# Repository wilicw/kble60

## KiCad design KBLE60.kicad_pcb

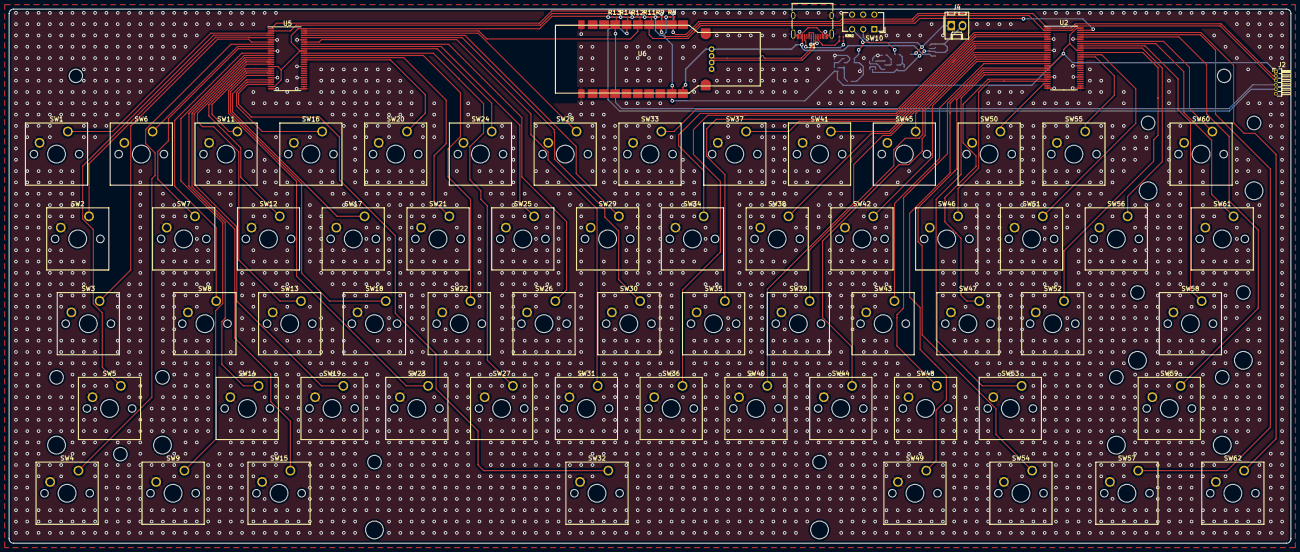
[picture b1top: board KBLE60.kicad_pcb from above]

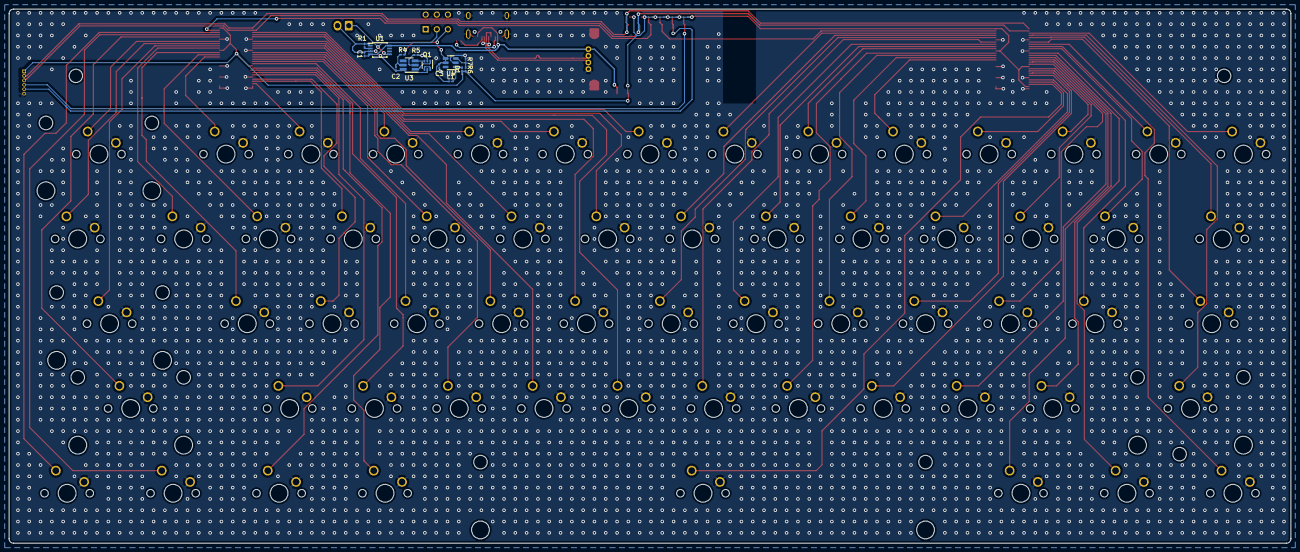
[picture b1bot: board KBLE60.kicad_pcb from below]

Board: 2 copper layers, 288.0 x 120.0 mm, 90 parts (14 on the bottom side), 85 nets.

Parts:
C1: 10u; C_0201_0603Metric_Pad0.64x0.40mm_HandSolder
C2, C3: 22u; C_0201_0603Metric_Pad0.64x0.40mm_HandSolder
D1: D_Schottky_Small; D_0201_0603Metric_Pad0.64x0.40mm_HandSolder
J1: USB_C_Receptacle_USB2.0; USB_C_Receptacle_XKB_U262-16XN-4BVC11
J2: Ext_pin; PinHeader_1x06_P1.00mm_Horizontal
J4: Battery; Molex_KK-254_AE-6410-02A_1x02_P2.54mm_Vertical
L1: 22u; L_0201_0603Metric_Pad0.64x0.40mm_HandSolder
Q1: Q_Dual_NMOS_G1S2G2D2S1D1; SOT-363_SC-70-6
R1, R7, R11, R12, R13, R14: 2k; R_0201_0603Metric_Pad0.64x0.40mm_HandSolder
R2, R3: 5k1; R_0201_0603Metric_Pad0.64x0.40mm_HandSolder
R4: 100; R_0201_0603Metric_Pad0.64x0.40mm_HandSolder
R5: 1k; R_0201_0603Metric_Pad0.64x0.40mm_HandSolder
R6: 10k; R_0201_0603Metric_Pad0.64x0.40mm_HandSolder
R8, R9: 4k7; R_0201_0603Metric_Pad0.64x0.40mm_HandSolder
SW1, SW6, SW7, SW8, SW11, SW12, SW13, SW14, SW16, SW17, SW18, SW19, SW20, SW21, SW22, SW23, SW24, SW25, SW26, SW27, SW28, SW29, SW30, SW31, SW33, SW34, SW35, SW36, SW37, SW38, SW39, SW40, SW41, SW42, SW43, SW44, SW45, SW46, SW47, SW48, SW50, SW51, SW52, SW53, SW55, SW56: SW_Push; SW_Cherry_MX_1.00u_PCB
SW2, SW61: SW_Push; SW_Cherry_MX_1.50u_PCB
SW3: SW_Push; SW_Cherry_MX_1.75u_PCB
SW4, SW9, SW15, SW49, SW54, SW57, SW62: SW_Push; SW_Cherry_MX_1.25u_PCB
SW5, SW58: SW_Push; SW_Cherry_MX_2.25u_PCB
SW10: SW_DPDT_x2; SW_CuK_JS202011AQN_DPDT_Angled
SW32: SW_Push; SW_Cherry_MX_6.25u_PCB
SW59: SW_Push; SW_Cherry_MX_2.75u_PCB
SW60: SW_Push; SW_Cherry_MX_2.00u_PCB
U1: tp4056; TSSOP-8_3x3mm_P0.65mm
U2, U5: PCA9506DGG,512; TSSOP-56_6.1x14mm_P0.5mm
U3: fs312f; SOT-23-6_Handsoldering
U4: MT3608; SOT-23-6
U6: nRF52840_dongle

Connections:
+BATT: J4.1, SW10.2 (B), U1.5 (BAT)
+VSW: C3.1, L1.1, R4.1, SW10.3 (C), U4.4 (EN), U4.5 (IN)
-BATT: C1.2, C2.2, J4.2, Q1.5 (S), R1.2, U1.1 (TEMP), U1.3 (GND), U3.6 (GND)
/K_0: SW45.1, U2.13 (IO1_0)
/K_1: SW6.1, U5.9 (IO0_5)
/K_2: SW11.1, U5.20 (IO1_6)
/K_3: SW16.1, U5.25 (IO2_2)
/K_4: SW20.1, U5.42 (IO3_5)
/K_5: SW24.1, U5.47 (IO4_1)
/K_6: SW28.1, U5.54 (IO4_7)
/K_7: SW33.1, U2.3 (IO0_0)
/K_8: SW37.1, U2.8 (IO0_4)
/K_9: SW41.1, U2.9 (IO0_5)
/K_': SW52.1, U2.45 (IO4_0)
/K_,: SW44.1, U2.15 (IO1_2)
/K_-: SW50.1, U2.26 (IO2_3)
/K_.: SW48.1, U2.19 (IO1_5)
/K_;: SW47.1, U2.24 (IO2_1)
/K_=: SW55.1, U2.43 (IO3_6)
/K_A: SW8.1, U5.12 (IO0_7)
/K_B: SW31.1, U5.50 (IO4_4)
/K_BSP: SW60.1, U2.50 (IO4_4)
/K_C: SW23.1, U5.21 (IO1_7)
/K_CAPLOCK: SW4.1, U5.8 (IO0_4)
/K_D: SW18.1, U5.22 (IO2_0)
/K_E: SW17.1, U5.24 (IO2_1)
/K_ESC: SW1.1, U5.3 (IO0_0)
/K_F: SW22.1, U5.44 (IO3_7)
/K_FN: SW57.1, U2.53 (IO4_6)
/K_G: SW26.1, U5.49 (IO4_3)
/K_H: SW30.1, U5.52 (IO4_5)
/K_I: SW38.1, U2.10 (IO0_6)
/K_J: SW35.1, U2.7 (IO0_3)
/K_K: SW39.1, U2.14 (IO1_1)
/K_L: SW43.1, U2.17 (IO1_4)
/K_LALT: SW15.1, U5.15 (IO1_2)
/K_LCTRL: SW3.1, U5.7 (IO0_3)
/K_LGUI: SW9.1, U5.13 (IO1_0)
/K_LSHIFT: SW5.1, U5.4 (IO0_1)
/K_M: SW40.1, U2.12 (IO0_7)
/K_N: SW36.1, U2.5 (IO0_2)
/K_O: SW42.1, U2.16 (IO1_3)
/K_P: SW46.1, U2.25 (IO2_2)
/K_Q: SW7.1, U5.10 (IO0_6)
/K_R: SW21.1, U5.43 (IO3_6)
/K_RALT: SW49.1, U2.20 (IO1_6)
/K_RCTRL: SW62.1, U2.54 (IO4_7)
/K_RETURN: SW58.1, U2.48 (IO4_2)
/K_RGUI: SW54.1, U2.21 (IO1_7)
/K_RSHIFT: SW59.1, U2.52 (IO4_5)
/K_S: SW13.1, U5.17 (IO1_4)
/K_SPACE: SW32.1, U5.26 (IO2_3)
/K_T: SW25.1, U5.48 (IO4_2)
/K_TAB: SW2.1, U5.5 (IO0_2)
/K_U: SW34.1, U2.4 (IO0_1)
/K_V: SW27.1, U5.45 (IO4_0)
/K_W: SW12.1, U5.19 (IO1_5)
/K_X: SW19.1, U5.16 (IO1_3)
/K_Y: SW29.1, U5.53 (IO4_6)
/K_Z: SW14.1, U5.14 (IO1_1)
/K_\: SW61.1, U2.49 (IO4_3)
/K_\{: SW51.1, U2.44 (IO3_7)
/K_\/: SW53.1, U2.22 (IO2_0)
/K_\}: SW56.1, U2.47 (IO4_1)
D+: J1.A6 (D+), J1.B6 (D+), U6.24 (D+)
D-: J1.A7 (D-), J1.B7 (D-), U6.25 (D-)
GND: C3.2, J1.A1 (GND), J1.A12 (GND), J1.B1 (GND), J1.B12 (GND), J1.S1 (SHIELD), J2.6, Q1.2 (S), R2.2, R3.2, R5.2, R7.2, SW1.2, SW2.2, SW3.2, SW4.2, SW5.2, SW6.2, SW7.2, SW8.2, SW9.2, SW11.2, SW12.2, SW13.2, SW14.2, SW15.2, SW16.2, SW17.2, SW18.2, SW19.2, SW20.2, SW21.2, SW22.2, SW23.2, SW24.2, SW25.2, SW26.2, SW27.2, SW28.2, SW29.2, SW30.2, SW31.2, SW32.2, SW33.2, SW34.2, SW35.2, SW36.2, SW37.2, SW38.2, SW39.2, SW40.2, SW41.2, SW42.2, SW43.2, SW44.2, SW45.2, SW46.2, SW47.2, SW48.2, SW49.2, SW50.2, SW51.2, SW52.2, SW53.2, SW54.2, SW55.2, SW56.2, SW57.2, SW58.2, SW59.2, SW60.2, SW61.2, SW62.2, U2.6 (VSS), U2.11 (VSS), U2.23 (VSS), U2.27 (A0), U2.28 (A1), U2.29 (A2), U2.30 (~OE), U2.34 (VSS), U2.39 (VSS), U2.51 (VSS), U4.2 (GND), U5.6 (VSS), U5.11 (VSS), U5.23 (VSS), U5.28 (A1), U5.29 (A2), U5.30 (~OE), U5.34 (VSS), U5.39 (VSS), U5.51 (VSS), U6.11 (GND), U6.12 (GND), U6.23 (GND)
INT1: R12.2, U5.55 (~INT), U6.6 (P0.22)
INT2: R11.2, U2.55 (~INT), U6.5 (P0.20)
INT_Ext1: J2.4, R13.2, U6.8 (P1.00)
INT_Ext2: J2.5, R14.2, U6.7 (P0.24)
unnamed: C2.1, R4.2, U3.5 (VCC)
unnamed: D1.2 (A), L1.2, U4.1 (SW)
unnamed: J1.A5 (CC1), R3.1
unnamed: J1.B5 (CC2), R2.1
unnamed: Q1.1 (G), U3.1 (OD)
unnamed: Q1.3 (G), U3.3 (OC)
unnamed: Q1.4 (D), Q1.6 (D)
unnamed: R1.1, U1.2 (PROG)
unnamed: R5.1, U3.2 (CS)
unnamed: R6.2, R7.1, U4.3 (FB)
SCL: J2.3, R9.2, U2.2 (SCL), U5.2 (SCL), U6.4 (P0.17)
SDA: J2.2, R8.2, U2.1 (SDA), U5.1 (SDA), U6.3 (P0.15)
VBUS: C1.1, J1.A4 (VBUS), J1.A9 (VBUS), J1.B4 (VBUS), J1.B9 (VBUS), U1.4 (VCC), U1.8 (CE), U6.21 (VBUS), U6.26 (VBUS)
VDD: D1.1 (K), J2.1, R6.1, R8.1, R9.1, R11.1, R12.1, R13.1, R14.1, U2.18 (VDD), U2.46 (VDD), U2.56 (~RESET), U5.18 (VDD), U5.27 (A0), U5.46 (VDD), U5.56 (~RESET), U6.20 (VDD_OUT)

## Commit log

2022-01-21 Create basic sch
2022-01-21 Remove DS_Store
2022-01-21 New gitignore
2022-01-21 battery charging ic
2022-01-21 Add protection ic
2022-01-21 Key switchs and pull ups
2022-01-21 Sch and footprints
2022-01-22 Layout
2022-01-22 Routing
2022-01-23 Via Stitching
2022-01-23 Improve tracing
